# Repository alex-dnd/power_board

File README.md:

# power_board — плата питания от аккумулятора 6S

Универсальная четырёхслойная плата питания. Питается от аккумулятора 6S (19,8–25,2 В) и выдаёт 7 В до 3 А, 5 В до 3 А и отдельный выход с напряжением батареи через самовосстанавливающийся предохранитель. Подписи выходов на плате (SERVO, POTOK, SK3500, ESP, RS485) остались от первого применения, использовать выходы можно для любой нагрузки в этих пределах.

Разведена вручную в KiCad 10.

## Выходы

| Разъём | Подпись | Напряжение | Откуда | Ток |
|---|---|---|---|---|
| J1 | BAT 6S | вход 19,8–25,2 В | аккумулятор | — |
| J2 | SERVO 7V | 7,06 В | LMR33630 (U2) | до 3 А |
| J3 | POTOK | напряжение батареи | через F2 1 А и FB1 | до 1 А |
| J4 | SK3500 | 5 В | U1 через LC-фильтр FB2 | до 1 А |
| J5 | ESP VIDEO | 5,02 В | LMR33630 (U1) | общие 3 А на J4–J7 |
| J6 | ESP SERVO | 5,02 В | U1 | |
| J7 | RS485 | 5,02 В | U1 | |

Квадратная площадка у каждого разъёма — «+», круглая — GND. Провода припаиваются в отверстия, клеммников нет.

## Схема

```
6S ─[F1 5 А]─[Q1 защита от переполюсовки]─[D2 TVS + C1 100 мкФ]─┬─ U1 LMR33630 → 5 В ─┬─ ESP32 ×2, RS485
                                                                │                      └─ FB2 + C19–C21 → SK3500
                                                                ├─ U2 LMR33630 → 7 В → сервопривод (D3 TVS, C15 470 мкФ)
                                                                └─ F2 1 А → FB1 → «Поток»
```

- U1 и U2: TI LMR33630BDDAR, 1,4 МГц, до 3 А. Номиналы обвязки взяты из [даташита TI](https://www.ti.com/lit/ds/symlink/lmr33630.pdf).
- Делитель 5 В: R2 100k / R3 24.9k. Делитель 7 В: R4 100k / R5 16.5k. Формула: Vout = 1 В × (1 + Rверх/Rниз).
- Защита от переполюсовки: P-канальный MOSFET Q1 SUD50P06-15, затвор через R1 на GND, стабилитрон D1 12 В ограничивает напряжение затвор–исток.

## Плата

| Параметр | Значение |
|---|---|
| Размер | 56,5 × 45 мм |
| Слои | 4: F.Cu сигналы + GND, In1 и In2 сплошная GND, B.Cu сигналы + GND |
| Толщина | 1,6 мм, фольга 35 мкм |
| Минимальная дорожка и зазор | 0,2 / 0,2 мм |
| Переходные отверстия | 0,6/0,3 и 0,8/0,4 мм |
| Дорожки SW → дроссель | 1,0 мм |
| Проверки | ERC 0, DRC 0 ошибок и 0 неразведённых (остались только предупреждения шелкографии) |

## Структура репозитория

```
kicad/   исходники KiCad: схема, плата, проект
gerber/  файлы для производства (Gerber + сверловка) и готовый архив power_board_gerber.zip
docs/    спецификация (BOM) и инструкция по заказу в Резоните
assembly/ файлы для заказа монтажа (BOM в Excel)
```

- [docs/zakaz_plat_rezonit.md](docs/zakaz_plat_rezonit.md) — как заказать платы в Резоните
- [docs/bom.md](docs/bom.md) — список деталей с номерами производителей

## Сборка и первое включение

- U1 и U2 имеют теплоотводящую площадку снизу. Паяльником их не припаять, нужен фен и паяльная паста.
- Первое включение делать от лабораторного блока питания: 20–24 В, ограничение тока 100–200 мА, без нагрузки. Проверить 5 В и 7 В мультиметром, только потом подключать нагрузку и аккумулятор.

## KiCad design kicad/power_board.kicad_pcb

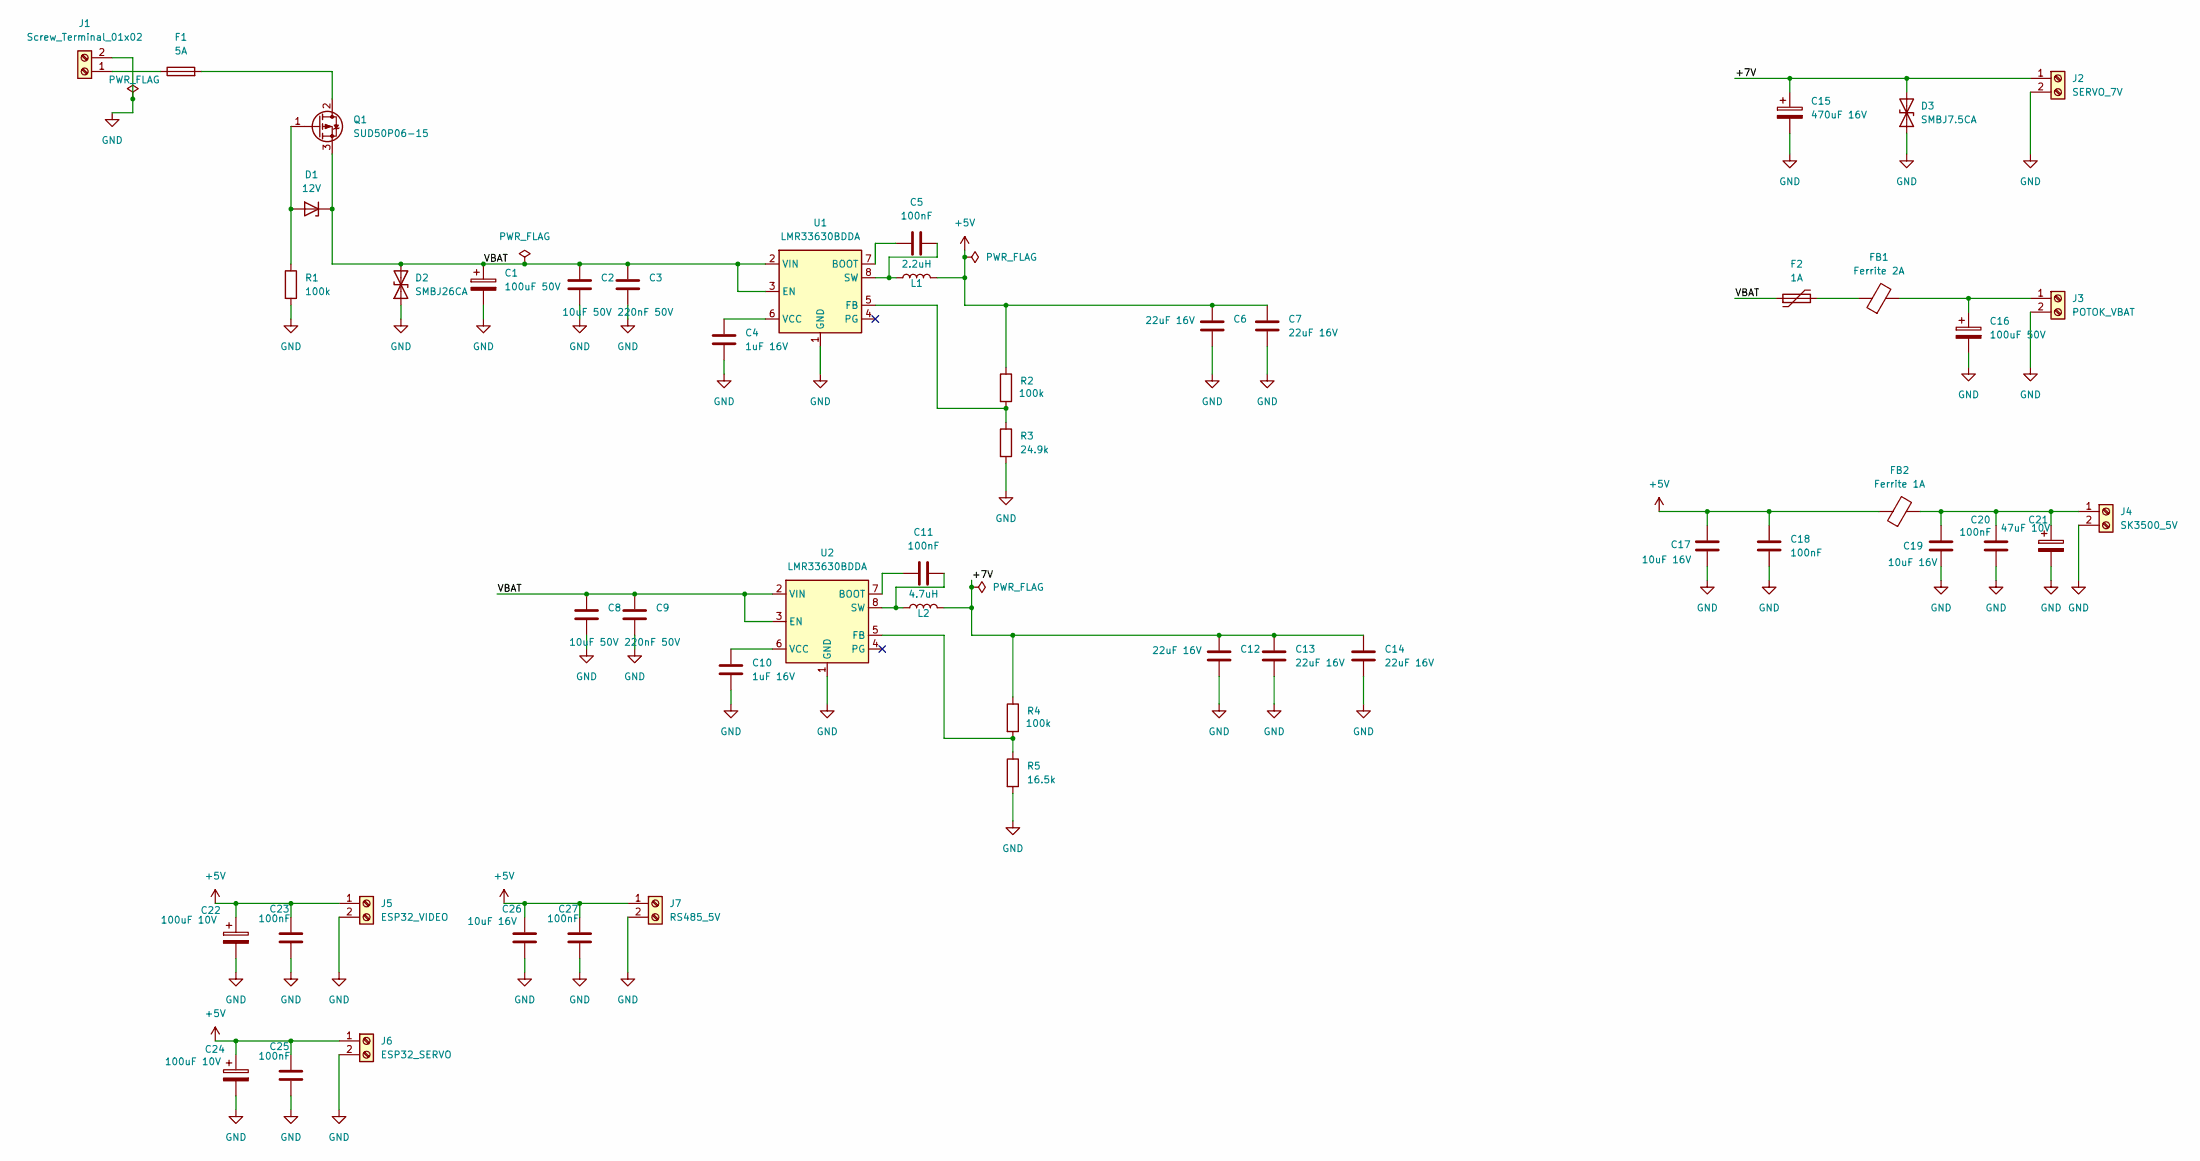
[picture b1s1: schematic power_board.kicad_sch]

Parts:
C1, C16: 100uF 50V; CP_Elec_10x10
C2, C8: 10uF 50V; C_1206_3216Metric
C3, C9: 220nF 50V; C_0805_2012Metric
C4, C10: 1uF 16V; C_0805_2012Metric
C5, C11, C18, C20, C23, C25, C27: 100nF; C_0805_2012Metric
C6, C7, C12, C13, C14: 22uF 16V; C_1206_3216Metric
C15: 470uF 16V; CP_Elec_8x10
C17, C19, C26: 10uF 16V; C_0805_2012Metric
C21: 47uF 10V; CP_Elec_5x5.4
C22, C24: 100uF 10V; CP_Elec_6.3x7.7
D1: 12V; D_SOD-123
D2: SMBJ26CA; D_SMB
D3: SMBJ7.5CA; D_SMB
F1: 5A; Fuse_1206_3216Metric
F2: 1A; Fuse_1812_4532Metric
FB1: Ferrite 2A; L_1206_3216Metric
FB2: Ferrite 1A; L_1206_3216Metric
J1: Screw_Terminal_01x02; SolderWire-0.5sqmm_1x02_P4.6mm_D0.9mm_OD2.1mm
J2: SERVO_7V; SolderWire-0.5sqmm_1x02_P4.6mm_D0.9mm_OD2.1mm
J3: POTOK_VBAT; SolderWire-0.25sqmm_1x02_P4.2mm_D0.65mm_OD1.7mm
J4: SK3500_5V; SolderWire-0.25sqmm_1x02_P4.2mm_D0.65mm_OD1.7mm
J5: ESP32_VIDEO; SolderWire-0.25sqmm_1x02_P4.2mm_D0.65mm_OD1.7mm
J6: ESP32_SERVO; SolderWire-0.25sqmm_1x02_P4.2mm_D0.65mm_OD1.7mm
J7: RS485_5V; SolderWire-0.25sqmm_1x02_P4.2mm_D0.65mm_OD1.7mm
L1: 2.2uH; L_Bourns_SRP7028A_7.3x6.6mm
L2: 4.7uH; L_Bourns_SRP7028A_7.3x6.6mm
Q1: SUD50P06-15; TO-252-2
R1, R2, R4: 100k; R_0805_2012Metric
R3: 24.9k; R_0805_2012Metric
R5: 16.5k; R_0805_2012Metric
U1, U2: LMR33630BDDA; Texas_HSOP-8-1EP_3.9x4.9mm_P1.27mm_ThermalVias

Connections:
+5V: C6.1, C7.1, C17.1, C18.1, C22.1, C23.1, C24.1, C25.1, C26.1, C27.1, FB2.1, J5.1, J6.1, J7.1, L1.2, R2.1
/+7V: C12.1, C13.1, C14.1, C15.1, D3.2 (A2), J2.1, L2.2, R4.1
/VBAT: C1.1, C2.1, C3.1, C8.1, C9.1, D1.1 (K), D2.2 (A2), F2.1, Q1.3 (S), U1.2 (VIN), U1.3 (EN), U2.2 (VIN), U2.3 (EN)
GND: C1.2, C2.2, C3.2, C4.2, C6.2, C7.2, C8.2, C9.2, C10.2, C12.2, C13.2, C14.2, C15.2, C16.2, C17.2, C18.2, C19.2, C20.2, C21.2, C22.2, C23.2, C24.2, C25.2, C26.2, C27.2, D2.1 (A1), D3.1 (A1), J1.2, J2.2, J3.2, J4.2, J5.2, J6.2, J7.2, R1.2, R3.2, R5.2, U1.1 (GND), U1.9 (GND), U2.1 (GND), U2.9 (GND)
unnamed: D1.2 (A), Q1.1 (G), R1.1
unnamed: F2.2, FB1.1
unnamed: F1.1, J1.1
unnamed: C16.1, FB1.2, J3.1
unnamed: C19.1, C20.1, C21.1, FB2.2, J4.1
unnamed: F1.2, Q1.2 (D)
unnamed: C5.1, U1.7 (BOOT)
unnamed: R2.2, R3.1, U1.5 (FB)
unnamed: C5.2, L1.1, U1.8 (SW)
unnamed: C4.1, U1.6 (VCC)
unnamed: C11.1, U2.7 (BOOT)
unnamed: R4.2, R5.1, U2.5 (FB)
unnamed: C11.2, L2.1, U2.8 (SW)
unnamed: C10.1, U2.6 (VCC)

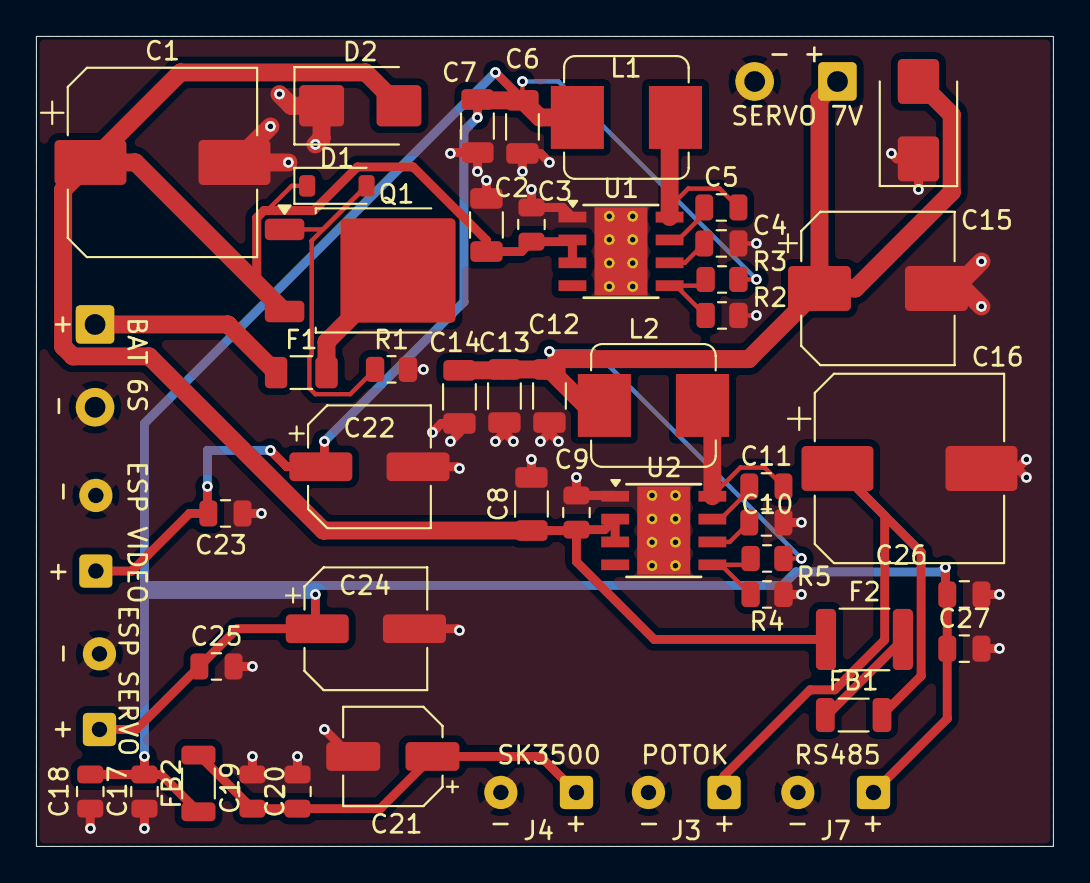
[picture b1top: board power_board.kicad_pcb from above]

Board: 4 copper layers, 56.5 x 45.0 mm, 51 parts (0 on the bottom side), 18 nets.
